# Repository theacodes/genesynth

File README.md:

# Genesynth

**Genesynth** is a music synthesizer module based around the Yamaha YM2612 FM Synthesis Chip, the same chip used in the Sega Genesis / Mega Drive.

## Why?

Because I wanted to. :)

## How?

This project is designed to use the Teensy 3.5 to control the YM2612 via USB MIDI.

More details for the hardware is available under the hardware folder, and more details on the firmware is under the firmware folder.

## License

This project is under the Apache License, Version 2.0. See LICENSE for more details.

If you use anything in this for a project, please let me know! I'd love to hear what you do with it. :)

# Building your own

This repository contains everything you'll need to build your own version of this synthesizer.

## Parts

You'll need to order all of the components in the three separate hardware modules under the `hardware` directory. You can use KiCAD to generate a BOM. These parts are readily available from Mouser and other distributors with the exception of the YM2612 chip - but this is easily obtainable on ebay.

Also note that you *must* use a Teensy 3.5. The Teensy 3.6 will *not* work as it's 3.3v logic and this design uses 5v logic.

You'll also need a 9v center-positive power supply.

## Ordering the PCBs

The gerbers for the PCBs are already created and are in the respective subdirectories under `hardware`. These are designed to fit within OSHPark's design rules, but I actually used PCBWay for my boards.

## Soldering components

You should *absolutely* use a socket for the YM2612 and the Teensy. Otherwise, this is all standard through-hole construction. Solder the smaller parts first followed by the larger parts.

## Connecting the boards.

There's three boards that make up the synth - the motherboard, a display board, and an audio board. The audio board connects to the *right* side of the motherboard, the display board to the *left*. You can connect these with wires or use pin headers and dupont connectors.

## Connect audio output.

The audo board has mono line out and stereo headphone out. You'll need to wire up the appropriate jack to the *right* side of the audio board.

## Assembling the case.

There's SVGs for creating a laser-cut case under `case`. You should be able to do this at any makerspace or using Ponoko. The case simply snaps together and the boards are mounted with standard M2 and M3 hardware.

## Preparing and programming the Teensy

Before powering on the synthesizer, **be sure to cut the USB power traces on the underside of the Teensy**. If you don't do this, **you will fry your board**. Once connected, you can build and upload the `firmware` using Teensyduino.

## Place patches on the SD card.

The synth needs patches on the SD card. Patches are in TFI format and many patch libraries are readily available. You should put patches into subdirectories of the SD card.

## All done!

You should now be able to boot the synthesizer, load patches, and play notes over MIDI. Have fun!

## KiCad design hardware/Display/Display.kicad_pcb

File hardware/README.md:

# Genesynth Hardware

The hardware consists of three major components: the motherboard, the audio amplifier, and the display board.

## Motherboard

The motherboard contains:

* The Teensy 3.5. The 3.5 was chosen due to its 5V operating voltage for ease of compatibility with the YM2612. A 3.6 could be used if logic-level converters were added.
* A pair of LDO Voltage Regulators. These take 9V power and step it down to independent 5V supplies for digital and analog components. Since this powers the Teensy, the Teensy's USB voltage lines *must be cut*.
* The YM2612 itself. This chip should be socketed in case of a bad or damaged chip.

## Audio Amplifier

The audio amplifier is a relatively straightforward summing amplifier and buffer using the TL074 and is modeled after the Mega Amp mod for the Sega Genesis. This lets the Genesynth match the sound of the original hardware fairly closely. It's designed using through-hole components because that is what I'm most comfortable with at this time, but could easily be done using surface-mount. The audio board is powered by a dedicated analog 5V line provided by one of the motherboard's LDOs to completely eliminate noise.

## Display board

The display board holds a simple OLED display module and provides 4 tac switches for displaying and navigating the menu.

## Shared Libraries

I used the [SparkFun KiCad Libraries](https://github.com/sparkfun/SparkFun-KiCad-Libraries) for some of the footprints.

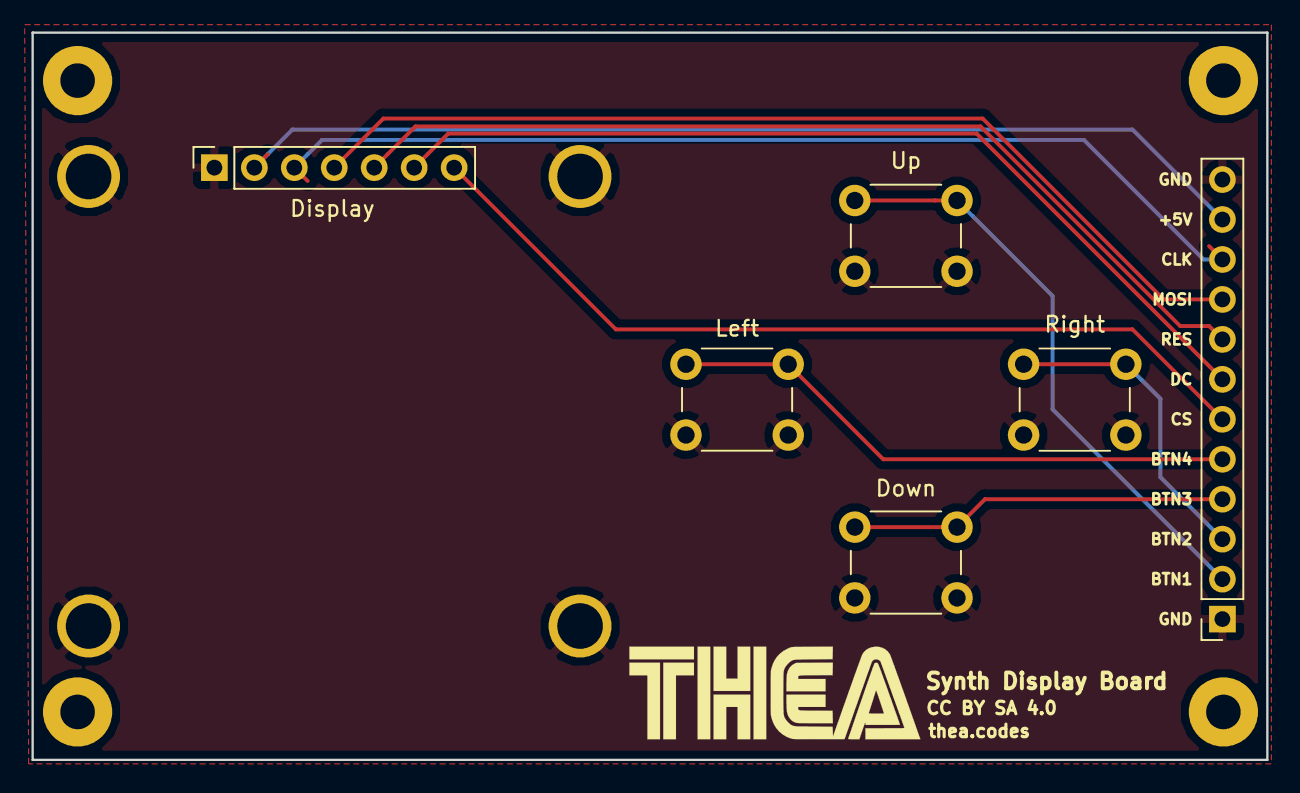
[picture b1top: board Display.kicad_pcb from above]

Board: 2 copper layers, 78.5 x 46.2 mm, 6 parts (0 on the bottom side), 11 nets.

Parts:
Display: SPI 128x64 SSH1106 OLED; OLED
Down: SW_Push; SW_PUSH_6mm_H9.5mm
J1: Motherboard Connector; PinSocket_1x12_P2.54mm_Vertical
Left: SW_Push; SW_PUSH_6mm_H9.5mm
Right: SW_Push; SW_PUSH_6mm_H9.5mm
Up: SW_Push; SW_PUSH_6mm_H9.5mm

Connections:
+5V: Display.2, J1.11
BUTTON_1: J1.2, Up.1
BUTTON_2: J1.3, Right.1
BUTTON_3: Down.1, J1.4
BUTTON_4: J1.5, Left.1
DISPLAY_CLK: Display.3, J1.10
DISPLAY_CS: Display.7, J1.6
DISPLAY_DC: Display.6, J1.7
DISPLAY_MOSI: Display.4, J1.9
DISPLAY_RES: Display.5, J1.8
GND: Display.1, Down.2, J1.1, J1.12, Left.2, Right.2, Up.2

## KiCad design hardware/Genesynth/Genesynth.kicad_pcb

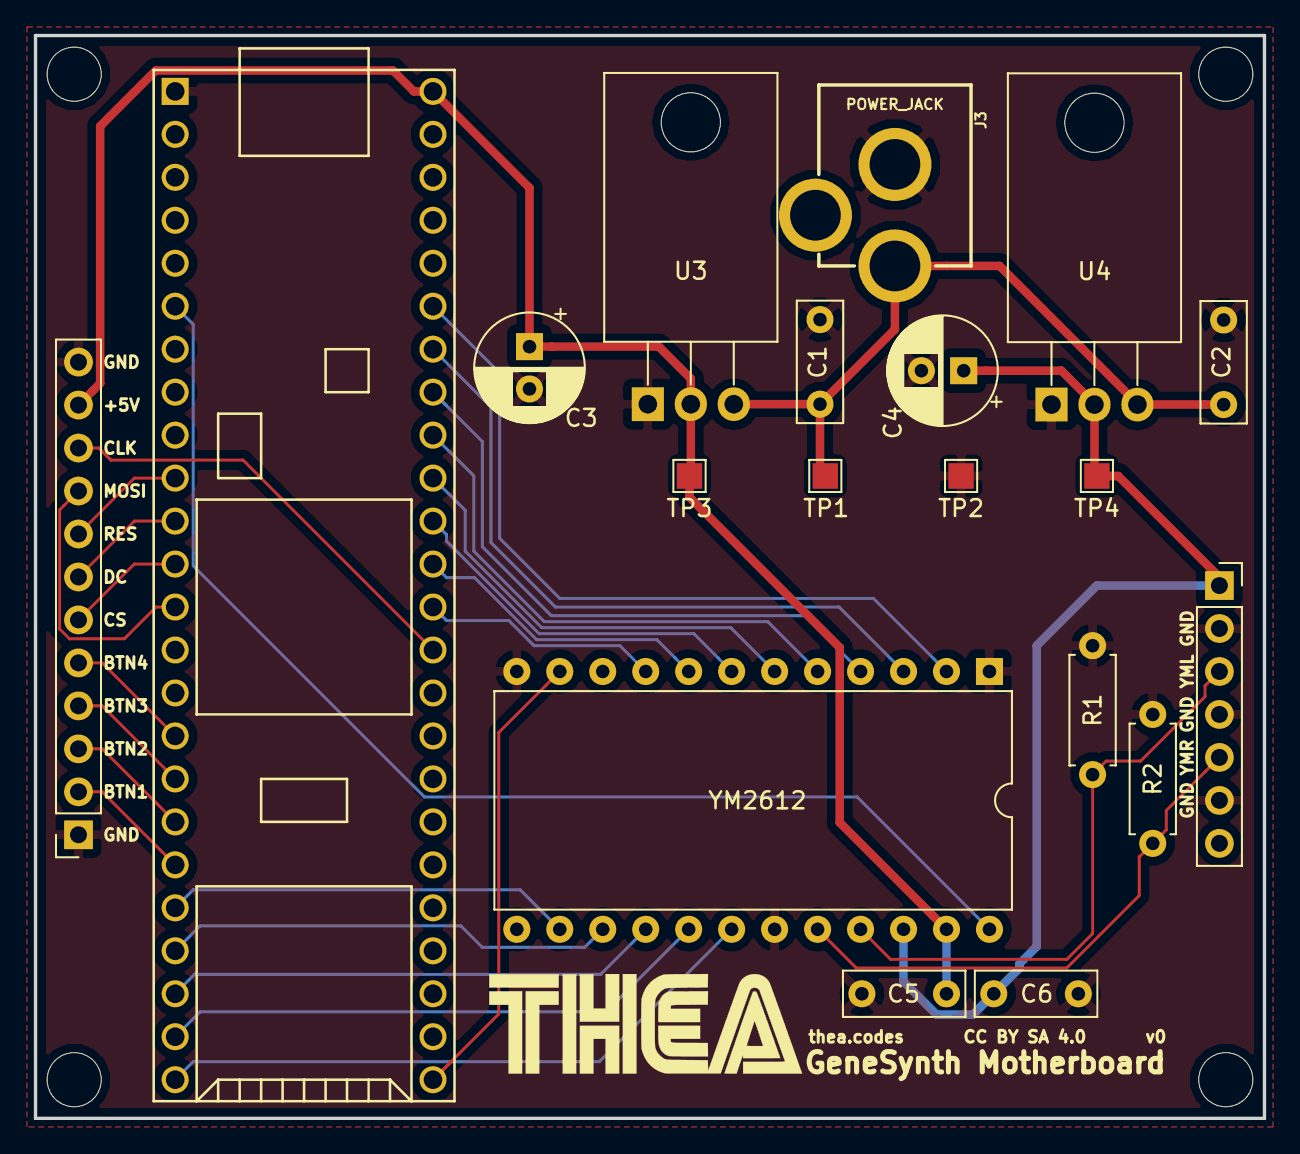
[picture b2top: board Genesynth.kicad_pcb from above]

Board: 2 copper layers, 72.6 x 64.0 mm, 19 parts (0 on the bottom side), 30 nets.

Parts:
C1, C2, C5, C6: 100nF; C_Disc_D7.0mm_W2.5mm_P5.00mm
C3, C4: 10uF; CP_Radial_D6.3mm_P2.50mm
J1: Audio Daughterboard; PinSocket_1x07_P2.54mm_Vertical
J2: Display Daughterboard; PinSocket_1x12_P2.54mm_Vertical
J3: POWER_JACK; POWER_JACK_PTH
R1, R2: 2.2k; R_Axial_DIN0207_L6.3mm_D2.5mm_P7.62mm_Horizontal
TP1, TP2, TP3, TP4: TestPoint; TestPoint_Pad_1.5x1.5mm
U1: Teensy3.5; TeensyReduced
U2: YM2612; DIP-24_W15.24mm
U3: LD1117S50 (Digital); TO-220-3_Horizontal_TabDown
U4: LD1117S50 (Analog); TO-220-3_Horizontal_TabDown

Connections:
+5V: C3.1, C5.1, J2.11, TP3.1, U1.53, U2.23, U3.2
+5VA: C4.1, C6.1, J1.1, TP4.1, U2.22, U4.2
+9V: C1.1, C2.1, J3.PWR, TP1.1, U3.3, U4.3
BUTTON_1: J2.2, U1.19
BUTTON_2: J2.3, U1.18
BUTTON_3: J2.4, U1.17
BUTTON_4: J2.5, U1.16
DISPLAY_CLK: J2.10, U1.40
DISPLAY_CS: J2.6, U1.12
DISPLAY_DC: J2.7, U1.11
DISPLAY_MOSI: J2.9, U1.13
DISPLAY_RES: J2.8, U1.10
Data0: U1.48, U2.2
Data1: U1.47, U2.3
Data2: U1.46, U2.4
Data3: U1.45, U2.5
Data4: U1.44, U2.6
Data5: U1.43, U2.7
Data6: U1.42, U2.8
Data7: U1.41, U2.9
GND: C1.2, C2.2, C3.2, C4.2, C5.2, C6.2, J1.2, J1.4, J1.6, J2.1, J2.12, J3.GND, R1.2, R2.2, TP2.1, U1.1, U2.1, U2.12, U2.19, U3.1, U4.1
YM_A0: U1.23, U2.17
YM_A1: U1.24, U2.18
YM_CLK: U1.6, U2.24
YM_CS: U1.20, U2.14
YM_IC: U1.30, U2.11
YM_L_RAW: J1.3, R1.1, U2.21
YM_RD: U1.22, U2.16
YM_R_RAW: J1.5, R2.1, U2.20
YM_WR: U1.21, U2.15

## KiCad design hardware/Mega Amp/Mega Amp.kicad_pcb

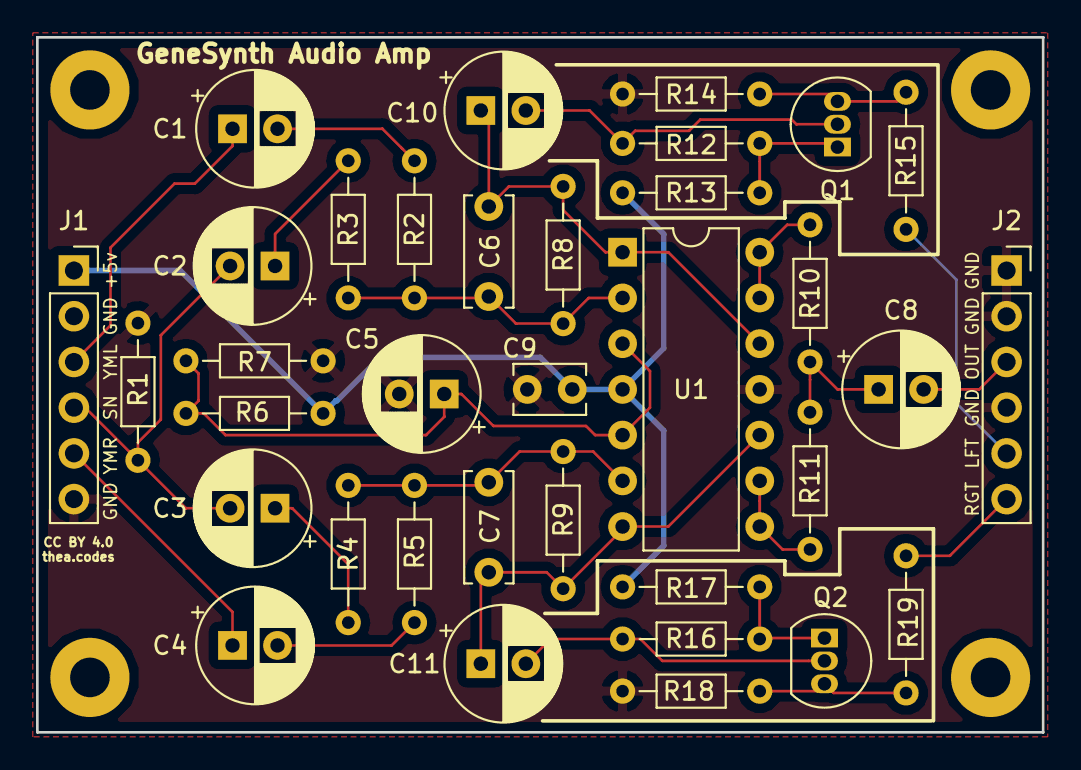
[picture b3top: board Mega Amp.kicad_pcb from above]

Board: 2 copper layers, 55.9 x 38.6 mm, 35 parts (0 on the bottom side), 26 nets.

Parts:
C1, C4: 10uF; CP_Radial_D6.3mm_P2.50mm
C2, C3: 1uF; CP_Radial_D6.3mm_P2.50mm
C5: 100uF; CP_Radial_D6.3mm_P2.50mm
C6: 270pF; C_Disc_D6.0mm_W2.5mm_P5.00mm
C7: 270pf; C_Disc_D6.0mm_W2.5mm_P5.00mm
C8, C10, C11: 220uF; CP_Radial_D6.3mm_P2.50mm
C9: 100nF; C_Disc_D3.8mm_W2.6mm_P2.50mm
J1, J2: Conn_01x06; PinSocket_1x06_P2.54mm_Vertical
Q1, Q2: BC547; TO-92_Inline
R1: R; R_Axial_DIN0204_L3.6mm_D1.6mm_P7.62mm_Horizontal
R2, R5: 51K; R_Axial_DIN0204_L3.6mm_D1.6mm_P7.62mm_Horizontal
R3, R4: 100K; R_Axial_DIN0204_L3.6mm_D1.6mm_P7.62mm_Horizontal
R6: 510; R_Axial_DIN0204_L3.6mm_D1.6mm_P7.62mm_Horizontal
R7: 750; R_Axial_DIN0204_L3.6mm_D1.6mm_P7.62mm_Horizontal
R8, R9: 160; R_Axial_DIN0204_L3.6mm_D1.6mm_P7.62mm_Horizontal
R10, R11, R14, R18: 330; R_Axial_DIN0204_L3.6mm_D1.6mm_P7.62mm_Horizontal
R12, R16: 75K; R_Axial_DIN0204_L3.6mm_D1.6mm_P7.62mm_Horizontal
R13, R17: 27; R_Axial_DIN0204_L3.6mm_D1.6mm_P7.62mm_Horizontal
R15, R19: 33; R_Axial_DIN0204_L3.6mm_D1.6mm_P7.62mm_Horizontal
U1: TL074; DIP-14_W7.62mm

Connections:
+5V: C9.1, J1.1, R6.2, R13.2, R17.2, U1.4
GND: C5.2, C9.2, J1.2, J1.6, J2.1, J2.2, J2.4, R1.1, R7.1, R14.2, R18.2, U1.11
HeadphoneLeft: J2.5, R15.2
HeadphoneRight: J2.6, R19.2
Mono: C8.2, J2.3
unnamed: C1.2, R2.2
unnamed: C2.1, R3.2
unnamed: C3.1, R4.2
unnamed: C4.2, R5.2
unnamed: C5.1, R6.1, R7.2, U1.3, U1.5
unnamed: C6.2, R2.1, R3.1, R8.2, U1.2
unnamed: C7.2, R4.1, R5.1, R9.2, U1.6
unnamed: C8.1, R10.1, R11.2
unnamed: C10.2, Q1.2, R12.1
unnamed: C11.2, Q2.2, R16.1
unnamed: Q1.1, R12.2, R13.1
unnamed: Q1.3, R14.1, R15.1
unnamed: Q2.1, R16.2, R17.1
unnamed: Q2.3, R18.1, R19.1
unnamed: R10.2, U1.13, U1.14
unnamed: R11.1, U1.8, U1.9
RawAudioLeft: C6.1, C10.1, R8.1, U1.1, U1.12
RawAudioRight: C7.1, C11.1, R9.1, U1.7, U1.10
SN: C2.2, C3.2, J1.4, R1.2
YMLeft: C1.1, J1.3
YMRight: C4.1, J1.5

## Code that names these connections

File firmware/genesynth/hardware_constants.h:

#ifndef THEA_HARDWARE_CONSTANTS_H
#define THEA_HARDWARE_CONSTANTS_H

#define STATUS_LED 13

/* YM2612 Constants */

// Pin 14-21 to YM DATA
// NOTE: The PCB motherboard reverses the order!
#define YM_DATA 21
// Pin 33 to YM IC
#define YM_IC 33
// Pin 32 to YM A1
#define YM_A1 32
// Pin 31 to YM A0
#define YM_A0 31
// Pin 30 to YM WR
#define YM_WR 29
// Pin 29 to YM CS
#define YM_CS 28
// Pin 28 to YM RD
#define YM_RD 30
// How long to hold the WR and CS lines when writing data.
// The datasheet indicates this should be *at least* 200nS, but it appears
// that a setting of (200) ~2,000uS ensures that the chip always gets our messages.
#define YM_WRITE_WAIT 11 // * 10uS
// The maximum about of uC cycles to wait for the YM2612 to be ready to receive data.
// This is around 10,000uS.
#define YM_MAX_WAIT_CYCLES 10000
// How long to hold the reset line.
// According to bus timing documents, we must hold the line low for at least
// 192 cycles. At 8hmz, that's 24 microseconds.
#define YM_RESET_WAIT 24 // uS
// The YM2612 clock is driven by a PWN pin
#define YM_CLOCK 4
/*
Ideal clock is 7.67, but it seems the teensy can't do that accurately.
Use 7.5, which is accurate & stable (verified by external tuner) & more
than close enough.
*/
#define YM_CLOCK_FREQ 7500000

/* Display & button constants */
// Display is on SPI.
#define DISPLAY_CS 10
#define DISPLAY_DC 9
#define DISPLAY_RESET 8
#ifndef DISPLAY_RATE
#define DISPLAY_RATE 66666 // 1/15th of a second in microseconds.
#endif
#ifndef U8G2_INITIALIZATION
#define U8G2_INITIALIZATION                                                                                            \
  U8G2_SH1106_128X64_NONAME_F_4W_HW_SPI u8g2(/* rotation=*/U8G2_R2, /* cs=*/DISPLAY_CS, /* dc=*/DISPLAY_DC,            \
                                             /* reset=*/DISPLAY_RESET);
#endif
// Buttons use descending pins from the first button's pin.
#define BUTTON_ONE 27

/* Synth core constants */
#define DEBUG_EEPROM_RW 0
#define EEPROM_PATCH_PRESENT_ADDR 0x09
#define EEPROM_PATCH_ADDR 0x10

#ifdef HARDWARE_CONSTANTS_OVERRIDE
#include "hardware_constants_override.h"
#endif

#endif

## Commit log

2018-06-16 Add PSG
2018-06-17 Working PSG using separate data bus for now
2018-06-18 Basic midi control of the PSG tone generators
2018-06-18 Simple note masking and velocity
2018-06-20 Remove velocity -> volume for now
2018-06-20 Basic YM2612 midi control
2018-06-21 Basic patch datastructure and polyphony
2018-06-26 Making the ym and psg share data pins, adding polyphony for the PSG
2018-06-28 Very very crappy opn parser
2018-07-04 Add thea easter egg
2018-07-04 Refactoring ym2612
2018-07-04 Refactoring vgm (broken)
2018-07-05 Refactor display
2018-07-05 Refactor psg
2018-07-05 Refactor opn parser
2018-07-05 Start writing a patch loader
2018-07-05 Basic patch loading working!
2018-07-05 6-channel polyphony
2018-07-23 Add ability to load OPM patches via midi program change
2018-07-24 Fix frequency calculation and refactor a bit
2018-07-25 Add basic status display
2018-08-13 Add the foundations of being able to control parameters over midi CC
2018-09-24 Starting basic interface for editing operator parameters
2018-10-07 Add schematic and PCB for the audio amplifier board
2018-10-07 Add debug for missing controlllers
2018-10-07 Somewhat working new timing protocol
2018-10-07 Cleanup some of the new timing protocol
2018-10-11 Add missing pulldown resistors
2018-10-14 Add motherboard
2018-10-14 Add note about PCB motherboard inverting direction of data pins
2018-10-14 Updating motherboard
2018-10-16 Added envelope edit screen and did some general cleanup
2018-10-18 Fix dumb bug in parsing the algorithm and feedback
2018-10-18 Add FM synth algorithm graphs
2018-10-19 Add display PCB
2018-10-25 Add PDF for Genesynth schematic
2018-10-25 Add PDFs for display and audio
2018-10-28 Switch to final hardware
2018-10-28 Update hardware pcbs
2018-10-29 Add buttons support and patch loading via buttons
    Closes #3
2018-10-29 Implement TFI patch loading, Closes #1
2018-10-30 Restore THEA bootsplash
2018-10-30 Wait on serial monitor when button 3 is pressed on boot
2018-11-01 Use clang-format
2018-11-01 Remove PSG
2018-11-01 Begin refactor synth core stuff
2018-11-01 Move CC mapping
2018-11-01 Moving env screen handling
2018-11-01 Fix bootup debug button
2018-11-02 Fix clock
2018-11-02 Add latency display for funsies
2018-11-17 Write up remaining operator modification values
2018-11-17 Oh my god... I am so stupid.
2018-11-17 Add detune, multiplier, rate scaling, and amplitude modulation screen
2018-11-17 Reformat
2018-11-20 Pitch bend support
2018-11-26 Added basic bank loading
2018-11-26 Handle bank change over midi
2018-11-26 Show bank name on patch screen
2018-11-26 Store last loaded program and bank in eeprom
2018-12-26 Foundation for using SysEx for parameter control
2018-12-28 Add basic FS iterators
2018-12-31 Basic string menu interface
2018-12-31 Working sketch of a menu controller
2018-12-31 Finally stupid file menu works
2018-12-31 File menu and submenu, yay!
2018-12-31 Refactoring
2018-12-31 Move firmware into its own folder
2018-12-31 More refactoring
2019-01-01 Add ambient UI stuff
2019-01-02 Remove dead display code
2019-01-03 Load the folder name when using the UI to load patches
2019-01-03 Allow overloading back()
2019-01-03 formatting
2019-01-03 Move eeprom stuff into synth.h
2019-01-05 Add a bit of documentation
2019-01-07 Move some stuff around
2019-01-07 Add hardware constants
2019-01-07 Move clock initialization
2019-01-07 Remove patch loading via midid, drop a lot of unused code
2019-01-07 Add tasks system and stats menu
2019-01-08 More stats
2019-01-08 Start of Mono/Poly modes
2019-01-08 Add Mono, Poly, and Unison modes, spread, and glide.
2019-01-11 Add proper note stack for unison mode
2019-01-11 Fix tiny bug
2019-01-14 Refactor note strategies into classes
2019-01-14 Removed dangling comment
2019-01-14 Add the polyphony menu to the UI
2019-01-14 Move operator parameters to NRPNs
2019-01-14 Fix Hz -> Chip Freq calculation
2019-01-15 Add MIDI CC mappings for mono, poly, unison, unison spread, glide enable, and glide amount.
2019-01-21 Add case design
2019-01-21 Some readme stuff
2019-01-21 Add link to the sparkfun library
2019-01-21 Add gerbers
2019-01-23 Add build guide
2019-01-24 Add patch saving via SysEx
2019-01-24 snake_cassssssssssse
2019-01-24 Add ctrlr panel
2019-04-30 Fix parameter direction and display
2019-04-30 Fix ctlr panel
2019-04-30 Add support for LFO
    Closes #16
2019-04-30 Small tweaks to the ctrlr panel
2019-04-30 Some file system QoL improvements
2019-04-30 Add easter egg to menu
2019-04-30 Expose algorithm and feedback over MIDI
2019-05-23 Add default value for lfo params
2019-05-23 Fix patch saving.
2019-07-01 Remove dead vgm code
2019-07-01 Fix various issues with compilation
2019-07-01 Get code compiling under clang with stubs for the hardware.
2019-07-02 Implement the display stuv
2019-07-02 Add button stub
2019-07-03 Implement filesystem stub
2019-07-03 Move simulator to top-level directory
2019-07-03 Simplify makefile
2019-07-03 Get audio emulation working
2019-07-03 Add basic MIDI support
2019-07-03 Make sim makefile build third-party stuff
2019-07-03 clang format the whole thing
2019-07-03 Remove sound test
2019-07-03 Implement EEPROM stub
2019-07-03 Don't prompt to select midi port if there is only one.
2019-07-04 Refactor sim code
2019-07-04 clang-format
2019-07-05 Add simulator (#22)
    * Get code compiling under clang with stubs for the hardware.
    * Implement the display stuv
    * Add button stub
    * Implement filesystem stub
    * Move simulator to top-level directory
    * Simplify makefile
2019-07-15 Make patch loading more robust and support nested directories
2019-07-16 Refactor out FileSelectMenu
2019-07-16 Add fsroot for simulator
2019-07-16 Open ./fsroot by default
2019-07-16 Skip '..' directory in simulator
2019-07-16 Fix bug in menu system
2019-07-16 Fix redefined macro
2019-07-16 Add midi CC message handling to the simulator
2019-07-16 Allow sending a test CC message via the keyboard in the simulator
2019-07-16 Extract draw_option from draw_menu_options
2019-07-16 Expose the last changed midi controller
2019-07-16 Implement the UI for parameter mapping
2019-07-17 Add support for mapping midi CCs to params
2019-07-17 Optimize the writing of operator parameters
2019-07-18 Add ring buffer to YM2612 I/O
2019-07-18 Update stats UI to accomodate new tasks
2019-07-19 Add ability to map velocity
2019-07-19 Add easing functions to custom mapped parameters
2019-07-20 Add range selection for params
2019-07-20 Reset mapping correctly
2019-08-11 Fix order of operators 2 and 3 in the alg gfx
2019-08-14 Add LFO screen
2019-08-14 Add note mode to ambient display
2019-09-18 Add sysex command to send the TFI data for the current patch
2019-09-18 Refactor the logic to normalize/denormalize values
2019-09-18 Fix small bug with OP 4 AM writes
2019-09-18 WIP: Delay note mode

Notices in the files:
hardware/Display/Display.kicad_pcb:
CC BY SA 4.0
hardware/Mega Amp/Mega Amp.kicad_pcb:
CC BY 4.0
